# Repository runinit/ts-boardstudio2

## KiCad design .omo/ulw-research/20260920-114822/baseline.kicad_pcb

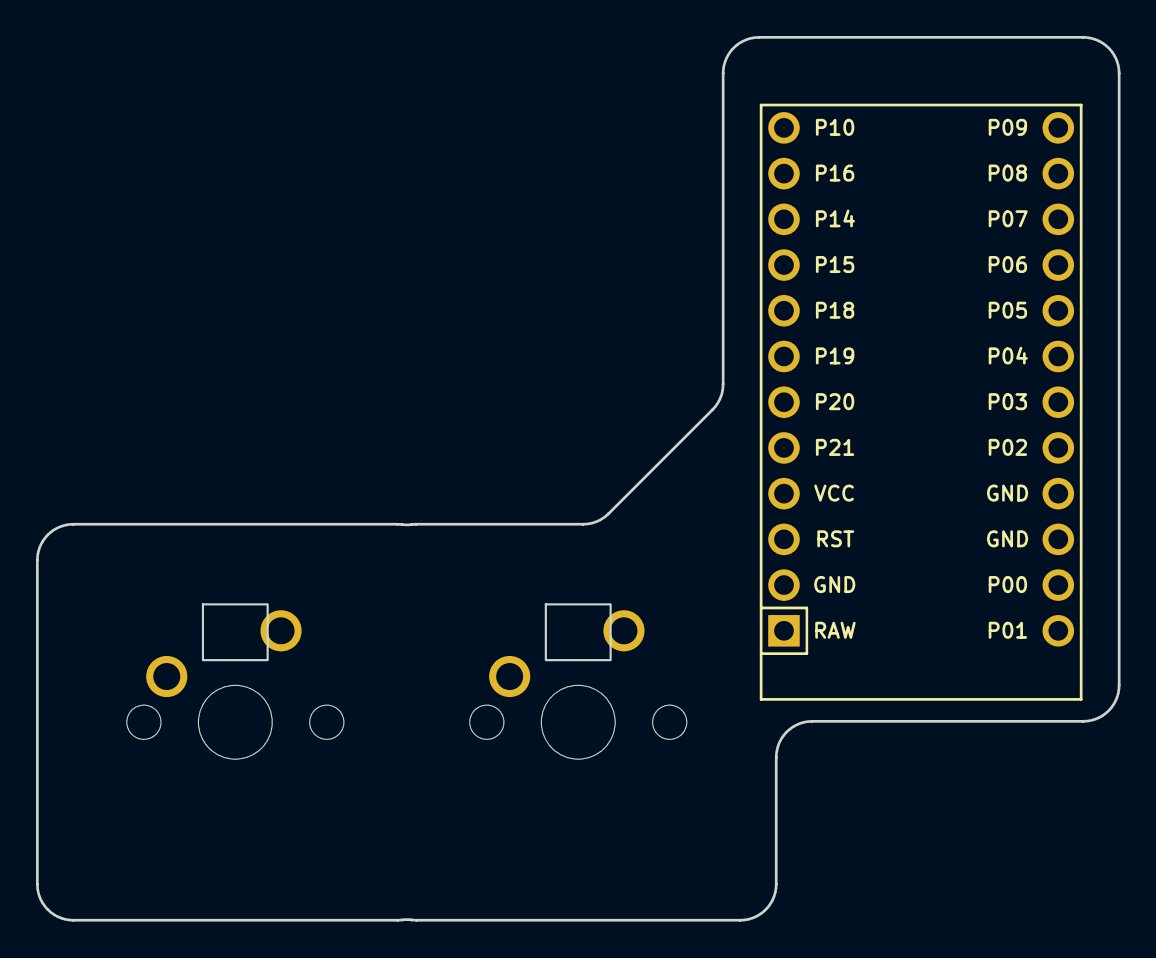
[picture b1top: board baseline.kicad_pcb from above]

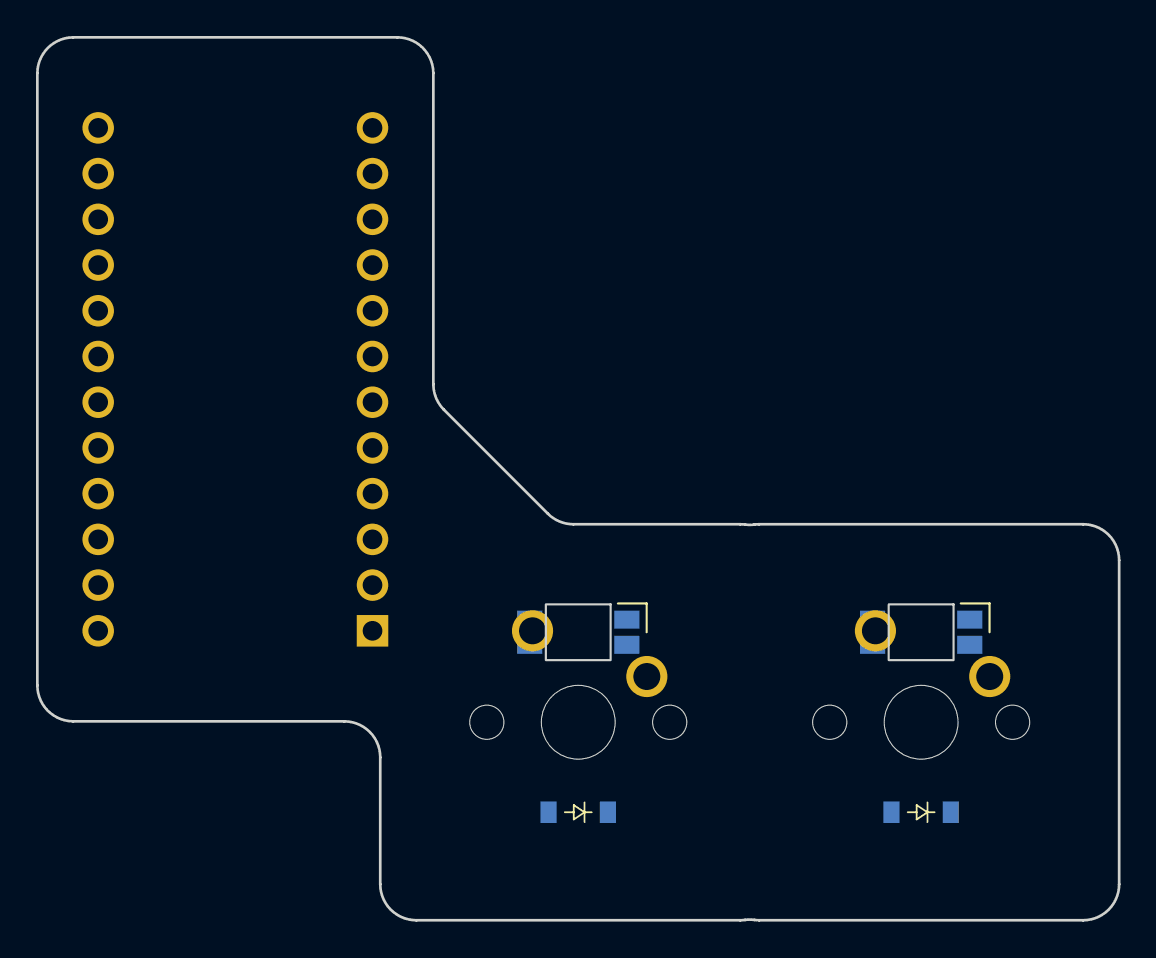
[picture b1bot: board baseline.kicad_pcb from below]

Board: 2 copper layers, 60.1 x 49.0 mm, 7 parts (6 on the bottom side), 9 nets, no tracks yet.

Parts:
X89fb0fa8, X881af91d: led_SK6812mini-e (per-keysingle-side)
X876ba2fe: switch_mx
X16970d43: ProMicro
Xc49a3d7b: diode_tht_sod123
Xec10466e: diode_tht_sod123
Xf89d51b7: switch_mx

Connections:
C1: X16970d43.14, Xf89d51b7.1
C2: X876ba2fe.1, X16970d43.13
GND: X89fb0fa8.3, X881af91d.3, X16970d43.2, X16970d43.15, X16970d43.16
LED_1: X89fb0fa8.2, X881af91d.4
LED_DATA: X89fb0fa8.4, X16970d43.18
R1: X16970d43.17, Xc49a3d7b.1, Xec10466e.1
VCC: X89fb0fa8.1, X881af91d.1, X16970d43.4
fingers_c1_r1_switch: Xec10466e.2, Xf89d51b7.2
fingers_c2_r1_switch: X876ba2fe.2, Xc49a3d7b.2

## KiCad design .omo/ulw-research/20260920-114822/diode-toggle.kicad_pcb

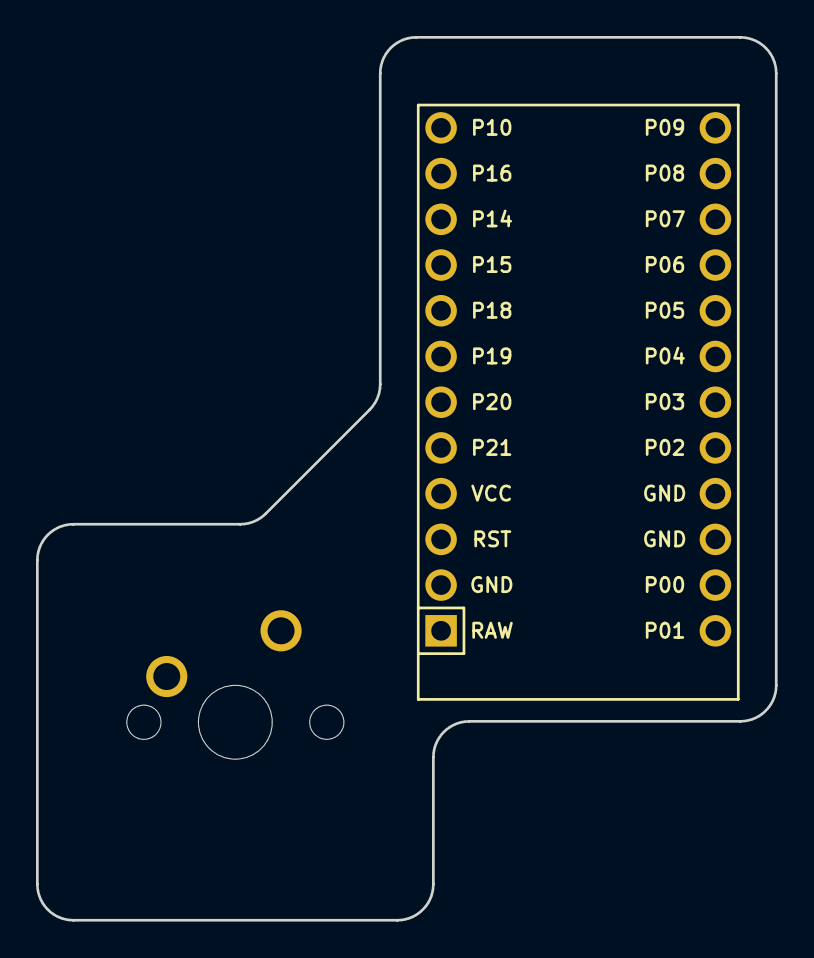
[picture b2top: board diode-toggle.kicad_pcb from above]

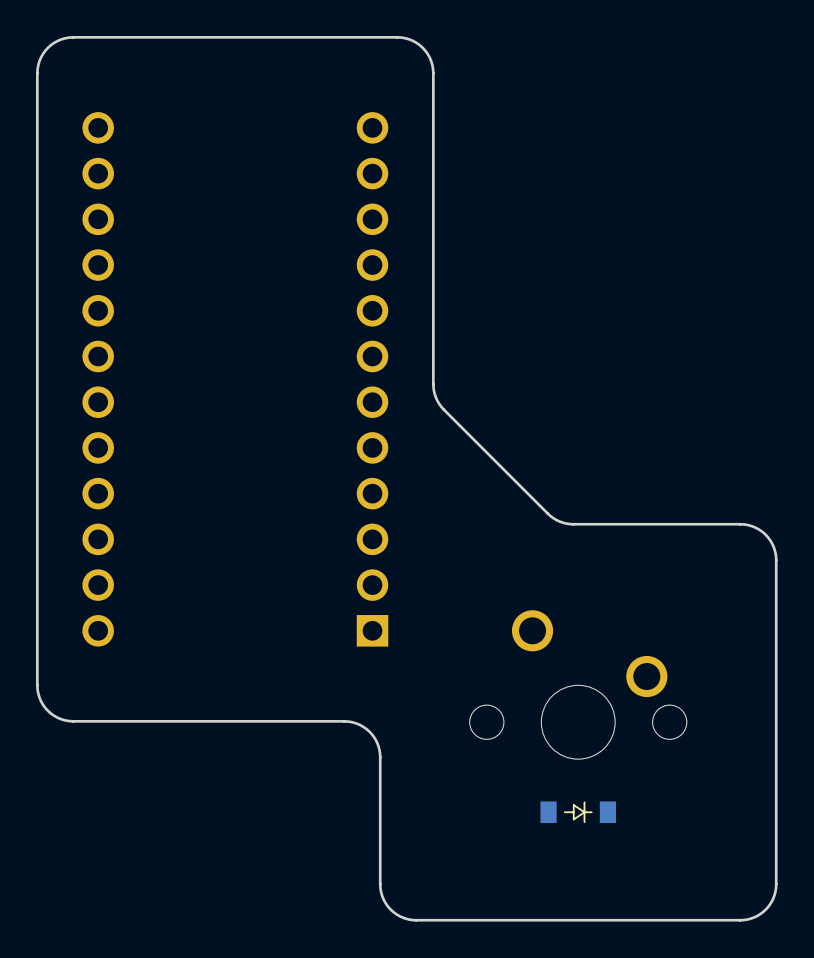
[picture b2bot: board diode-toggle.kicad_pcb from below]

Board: 2 copper layers, 41.0 x 49.0 mm, 3 parts (2 on the bottom side), 3 nets, no tracks yet.

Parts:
X16970d43: ProMicro
Xec10466e: diode_tht_sod123
Xf89d51b7: switch_mx

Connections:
C1: X16970d43.14, Xf89d51b7.1
GND: X16970d43.2, X16970d43.15, X16970d43.16
R1: X16970d43.13, Xec10466e.1
